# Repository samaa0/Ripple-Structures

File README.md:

# Ripple Structures

**DWM3000 Ultra-Wideband 4D Indoor Positioning, Gesture Recognition, and Unity Visualization**

Ripple Structures is an indoor sensing project built around DWM3000 ultra-wideband ranging modules. It combines Arduino receiver/transmitter firmware, a Python real-time positioning and plotting server, ML gesture-recognition scripts, a Unity visualizer, and custom PCB/case hardware.

## Demo

[Watch the main real-time 3D positioning demo](docs/media/ripple-structures-demo.mp4), or open the individual demo clips below. These clips were extracted from the final presentation and arranged as separate sessions in [docs/demo.md](docs/demo.md). The private scanned Unity room scene and PowerPoint Media 4 are intentionally excluded.

| Session | Demo |
| --- | --- |
| Real-time 3D positioning |  |
| Gesture recognition prediction |  |
| Boundary triggering in Unity |  |
| Two-receiver LED boundary triggering |  |

## System Overview

- `firmware/transmitter/` sends DWM3000 UWB ranging messages from mobile transmitter nodes.
- `firmware/receiver/` receives DWM3000 UWB range measurements, applies per-anchor calibration, and forwards measurements over WiFi/UDP.
- `software/positioning_server/` estimates receiver position, filters samples, plots live data, and forwards coordinates to Unity.
- `software/ml/` contains the final computing, model training, model testing, fusion, and plotting scripts.
- `unity/ripple-visualizer/` contains the reusable Unity scripts and project configuration for visualizing tracked users.
- `hardware/` contains DWM3000/ESP32-C3 PCB design files, reference Gerbers, and 3D-printable enclosure files.

## Architecture

Core diagrams are included in [docs/architecture.md](docs/architecture.md):

## Quick Start

1. Copy `firmware/transmitter/config.example.h` to `firmware/transmitter/config.h`, set the DWM3000 transmitter ID, and flash `transmitter.ino`.
2. Copy `firmware/receiver/config.example.h` to `firmware/receiver/config.h`, set WiFi/network details, DWM3000 anchor coordinates, calibration offsets, and flash `receiver.ino`.
3. Install Python dependencies and run the positioning server from `software/positioning_server/`.
4. Open `unity/ripple-visualizer/` with Unity `2022.3.10f1`, create or import a neutral scene, and attach the included receiver/UDP scripts.

## Firmware Setup

The committed firmware excludes private credentials. Local `config.h` files are ignored by Git.

```sh
cp firmware/transmitter/config.example.h firmware/transmitter/config.h
cp firmware/receiver/config.example.h firmware/receiver/config.h
```

Edit the copied receiver config with your WiFi SSID/password, positioning server IP, UDP port, transmitter coordinates, receiver ID, and calibration offsets.

## Python Setup

Positioning server:

```sh
cd software/positioning_server
python3 -m venv .venv
source .venv/bin/activate
pip install -r requirements.txt
python positioning_server.py
```

Runtime settings can be provided through environment variables; see `config.example.yaml` and [software/positioning_server/README.md](software/positioning_server/README.md).

ML/computing scripts live in `software/ml/`. Final model artifacts are stored in `software/ml/models/`. Raw CSV datasets are not included; expected schemas are documented in [software/ml/data/README.md](software/ml/data/README.md).

## Unity Setup

Open `unity/ripple-visualizer/` in Unity `2022.3.10f1`. The public release includes scripts, materials, Unity packages, and project settings, but excludes the original private scanned room scene and object meshes. Create a neutral scene or import your own room model, then attach the UDP receiver and collision scripts as needed.

## PCB And Case

Hardware files for the DWM3000-based positioning nodes are under `hardware/`:

- `hardware/pcb/altium-final/` has the final Altium project, PCB, schematic, BOM document, and structure file.
- `hardware/pcb/eagle-esp32c3-final/` has the ESP32-C3/DWM3000 Eagle board and schematic.
- `hardware/pcb/gerber-reference/` has reference Gerber outputs.
- `hardware/case/` has STL/STP case files.

## Licenses

Project-authored software and documentation are released under the MIT License. Included third-party/vendor files retain their original notices. Hardware design files are released under CERN-OHL-S-2.0; see [hardware/LICENSE-CERN-OHL-S-2.0.txt](hardware/LICENSE-CERN-OHL-S-2.0.txt).

## Privacy And Security

Private scanned Unity room scenes, room/object meshes, raw report files, personal metadata, WiFi credentials, local paths, raw training datasets, logs, virtual environments, and backups are intentionally excluded from this public release.

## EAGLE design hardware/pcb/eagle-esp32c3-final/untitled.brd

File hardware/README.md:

# Hardware

The hardware release contains DWM3000-based PCB design sources, reference fabrication outputs, and 3D-printable case files.

## PCB

- `pcb/altium-final/` contains the final DWM3000 Altium project files.
- `pcb/eagle-esp32c3-final/` contains the ESP32-C3/DWM3000 Eagle board and schematic.
- `pcb/gerber-reference/` contains reference Gerber outputs from an earlier exported project.

## Case

`case/` contains STL/STP enclosure files:

- `shouhuan.stl`
- `UWB.stl`
- `shouh.stp`
- `UWB only case.stl`

## License

Hardware design files are released under CERN-OHL-S-2.0. See `LICENSE-CERN-OHL-S-2.0.txt`.

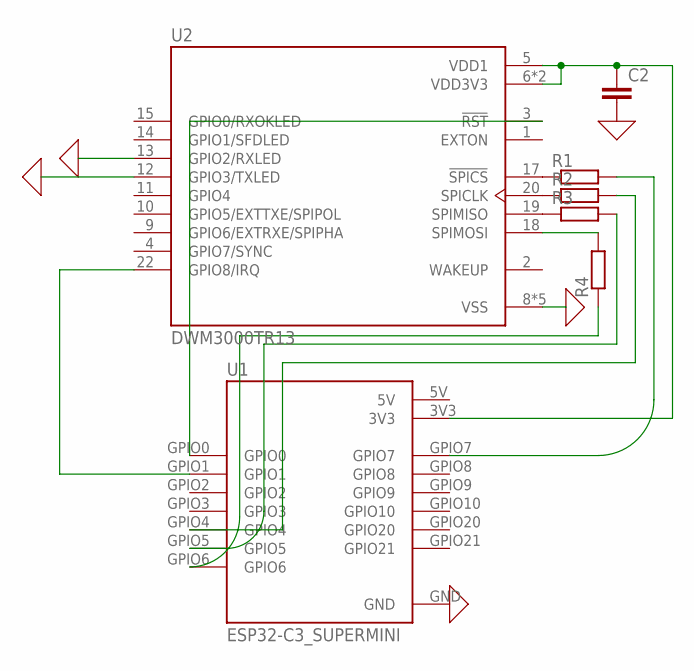
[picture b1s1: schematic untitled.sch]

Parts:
C2: C-EUC0402K; C0402K
R1, R2, R3, R4: SMK
U1: ESP32-C3_SUPERMINI; MODULE_ESP32-C3_SUPERMINI
U2: DWM3000TR13; XCVR_DWM3000TR13

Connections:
0: C2.2, U1.GND, U2.8 (VSS), U2.12 (GPIO3/TXLED), U2.13 (GPIO2/RXLED), U2.16 (VSS), U2.21 (VSS), U2.23 (VSS), U2.24 (VSS)
5V: U1.5V
unnamed: U1.GPIO1, U2.22 (GPIO8/IRQ)
unnamed: C2.1, U1.3V3, U2.5 (VDD1), U2.6 (VDD3V3), U2.7 (VDD3V3)
unnamed: U1.GPIO0, U2.3 (!RST)
unnamed: R1.2, U2.17 (!SPICS)
unnamed: R1.1, U1.GPIO7
unnamed: R2.2, U2.20 (SPICLK)
unnamed: R2.1, U1.GPIO4
unnamed: R3.2, U2.19 (SPIMISO)
unnamed: R3.1, U1.GPIO5
unnamed: R4.1, U2.18 (SPIMOSI)
unnamed: R4.2, U1.GPIO6

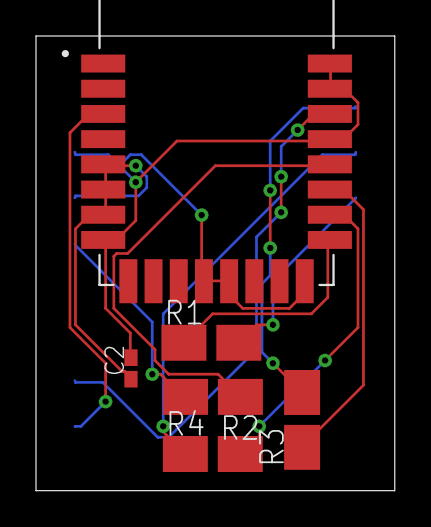
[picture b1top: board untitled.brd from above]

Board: 2 copper layers, 19.9 x 25.3 mm, 7 parts (1 on the bottom side), 12 nets.
